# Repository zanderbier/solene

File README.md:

solene
======

Arduino Solenoid Driver

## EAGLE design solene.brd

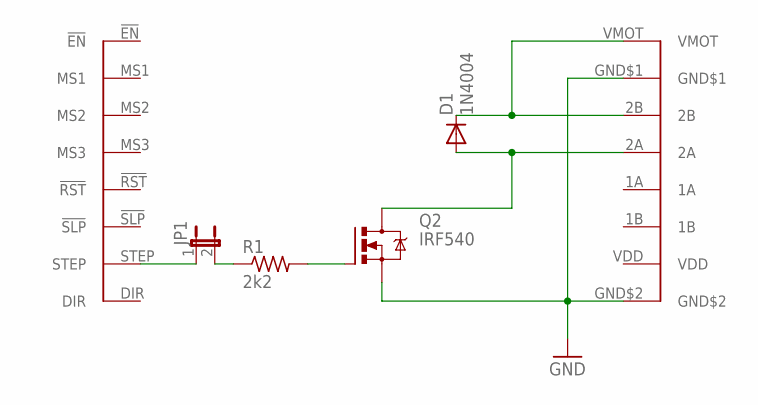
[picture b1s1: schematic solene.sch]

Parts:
D1: 1N4004; D-2.5
J1X: CLONOLU
JP1: JUMPER-2PTH; 1X02
Q2: IRF540; TO220BV
R1: 2k2; 0204V

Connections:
GND: J1X.GND$1, J1X.GND$2, Q2.S
unnamed: J1X.STEP, JP1.1
unnamed: JP1.2, R1.1
unnamed: Q2.G, R1.2
unnamed: D1.C, J1X.2B, J1X.VMOT
unnamed: D1.A, J1X.2A, Q2.D
VDD: J1X.VDD

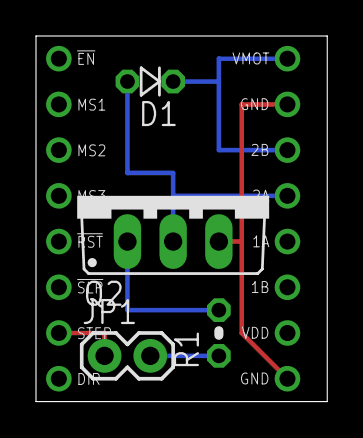
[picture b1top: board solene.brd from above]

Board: 2 copper layers, 16.2 x 20.3 mm, 5 parts (0 on the bottom side), 6 nets.

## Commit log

2014-04-30 sch brd
2014-05-02 rev 1
2014-05-02 rev 1a
2014-05-03 SMD Version

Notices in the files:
parts and their libraries:
SparkFun-Passives: Licensing: CC v3.0 Share-Alike You are welcome to use this library for commercial purposes.
